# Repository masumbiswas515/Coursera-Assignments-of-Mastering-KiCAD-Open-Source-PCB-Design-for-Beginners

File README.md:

# Coursera-Assignments-of-Mastering-KiCAD-Open-Source-PCB-Design-for-Beginners
This respiratory consists of the peer graded assignments of the Coursera course, Mastering KiCAD: Open-Source PCB Design for Beginners.

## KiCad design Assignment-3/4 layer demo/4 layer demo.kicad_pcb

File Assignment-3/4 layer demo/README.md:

This folder contains all the KiCAD files.

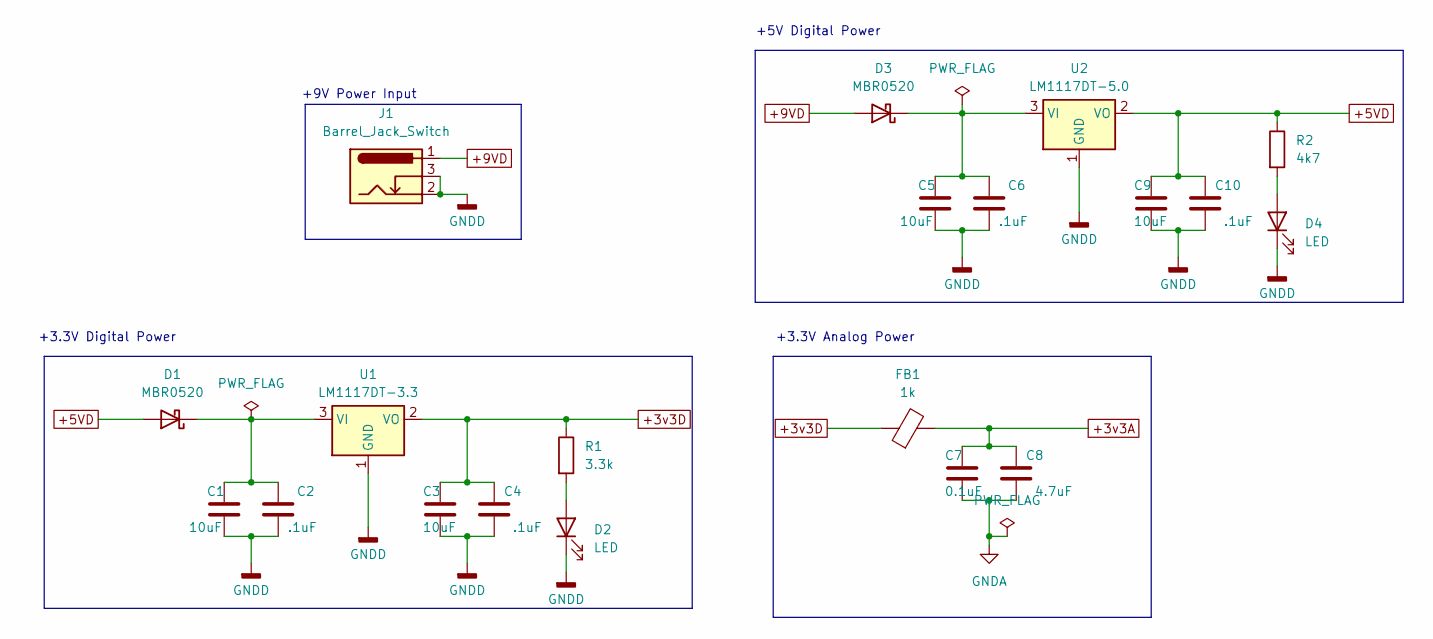
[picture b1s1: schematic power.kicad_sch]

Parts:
C1, C3, C5, C9: 10uF; C_0603_1608Metric
C2, C4, C6, C10: .1uF; C_0603_1608Metric
C7: 0.1uF; C_0603_1608Metric
C8: 4.7uF; C_0603_1608Metric
D1, D3: MBR0520; D_SOD-123
D2, D4: LED; LED_0603_1608Metric
FB1: 1k; L_0603_1608Metric
J1: Barrel_Jack_Switch; BarrelJack_Horizontal
R1: 3.3k; R_0603_1608Metric
R2: 4k7; R_0603_1608Metric
U1: LM1117DT-3.3; TO-252-3_TabPin2
U2: LM1117DT-5.0; TO-252-3_TabPin2

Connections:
+3v3A: C7.1, C8.1, FB1.2; also elsewhere on the board
+3v3D: C3.1, C4.1, FB1.1, R1.1, U1.2 (VO); also elsewhere on the board
+5VD: C9.1, C10.1, D1.2 (A), R2.1, U2.2 (VO)
+9VD: D3.2 (A), J1.1
GNDA: C7.2, C8.2; also elsewhere on the board
GNDD: C1.2, C2.2, C3.2, C4.2, C5.2, C6.2, C9.2, C10.2, D2.1 (K), D4.1 (K), J1.2, J1.3, U1.1 (GND), U2.1 (GND); also elsewhere on the board
unnamed: C1.1, C2.1, D1.1 (K), U1.3 (VI)
unnamed: D2.2 (A), R1.2
unnamed: C5.1, C6.1, D3.1 (K), U2.3 (VI)
unnamed: D4.2 (A), R2.2

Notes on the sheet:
+5V Digital Power
+9V Power Input
+3.3V Digital Power
+3.3V Analog Power

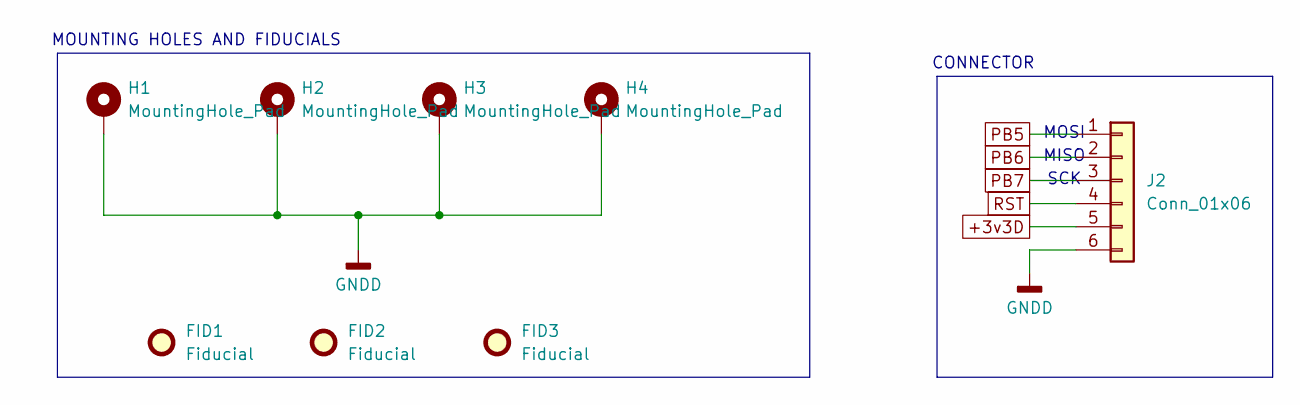
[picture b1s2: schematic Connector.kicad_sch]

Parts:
FID1, FID2, FID3: Fiducial; Fiducial_0.5mm_Mask1.5mm
H1, H2, H3, H4: MountingHole_Pad; MountingHole_2.2mm_M2_DIN965_Pad
J2: Conn_01x06; PinHeader_1x06_P1.00mm_Vertical

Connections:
+3v3D: J2.5; also elsewhere on the board
GNDD: H1.1, H2.1, H3.1, H4.1, J2.6; also elsewhere on the board
PB5: J2.1; also elsewhere on the board
PB6: J2.2; also elsewhere on the board
PB7: J2.3; also elsewhere on the board
RST: J2.4; also elsewhere on the board

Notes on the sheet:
MOSI
CONNECTOR
MOUNTING HOLES AND FIDUCIALS
SCK
MISO

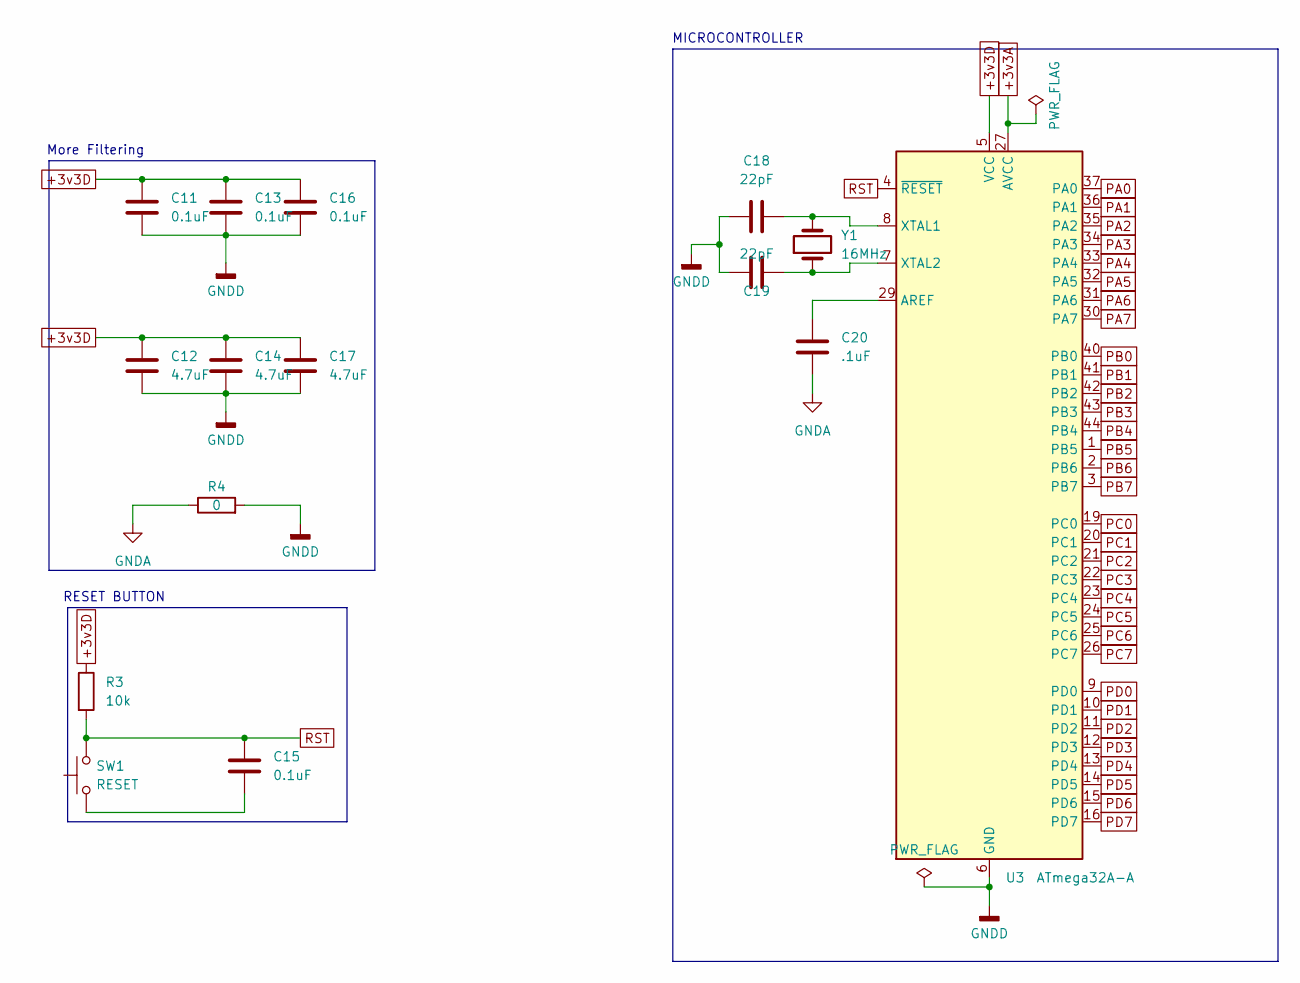
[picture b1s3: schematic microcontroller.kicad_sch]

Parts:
C11, C13, C15, C16: 0.1uF; C_0603_1608Metric
C12, C14, C17: 4.7uF; C_0603_1608Metric
C18, C19: 22pF; C_0603_1608Metric
C20: .1uF; C_0603_1608Metric
R3: 10k; R_0603_1608Metric
R4: 0; R_0603_1608Metric
SW1: RESET; SW_PUSH_6mm_H4.3mm
U3: ATmega32A-A; TQFP-44_10x10mm_P0.8mm
Y1: 16MHz; Crystal_SMD_0603-2Pin_6.0x3.5mm

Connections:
+3v3A: U3.27 (AVCC); also elsewhere on the board
+3v3D: C11.1, C12.1, C13.1, C14.1, C16.1, C17.1, R3.1, U3.5 (VCC), U3.17 (VCC), U3.38 (VCC); also elsewhere on the board
GNDA: C20.2, R4.1; also elsewhere on the board
GNDD: C11.2, C12.2, C13.2, C14.2, C16.2, C17.2, C18.1, C19.1, R4.2, U3.6 (GND), U3.18 (GND), U3.28 (GND), U3.39 (GND); also elsewhere on the board
unnamed: C15.2, SW1.1
unnamed: C20.1, U3.29 (AREF)
unnamed: C18.2, U3.8 (XTAL1), Y1.2
unnamed: C19.2, U3.7 (XTAL2), Y1.1
PA0: U3.37 (PA0)
PA1: U3.36 (PA1)
PA2: U3.35 (PA2)
PA3: U3.34 (PA3)
PA4: U3.33 (PA4)
PA5: U3.32 (PA5)
PA6: U3.31 (PA6)
PA7: U3.30 (PA7)
PB0: U3.40 (PB0)
PB1: U3.41 (PB1)
PB2: U3.42 (PB2)
PB3: U3.43 (PB3)
PB4: U3.44 (PB4)
PB5: U3.1 (PB5); also elsewhere on the board
PB6: U3.2 (PB6); also elsewhere on the board
PB7: U3.3 (PB7); also elsewhere on the board
PC0: U3.19 (PC0)
PC1: U3.20 (PC1)
PC2: U3.21 (PC2)
PC3: U3.22 (PC3)
PC4: U3.23 (PC4)
PC5: U3.24 (PC5)
PC6: U3.25 (PC6)
PC7: U3.26 (PC7)
PD0: U3.9 (PD0)
PD1: U3.10 (PD1)
PD2: U3.11 (PD2)
PD3: U3.12 (PD3)
PD4: U3.13 (PD4)
PD5: U3.14 (PD5)
PD6: U3.15 (PD6)
PD7: U3.16 (PD7)
RST: C15.1, R3.2, SW1.2, U3.4 (~RESET); also elsewhere on the board

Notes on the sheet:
MICROCONTROLLER
RESET BUTTON
More Filtering

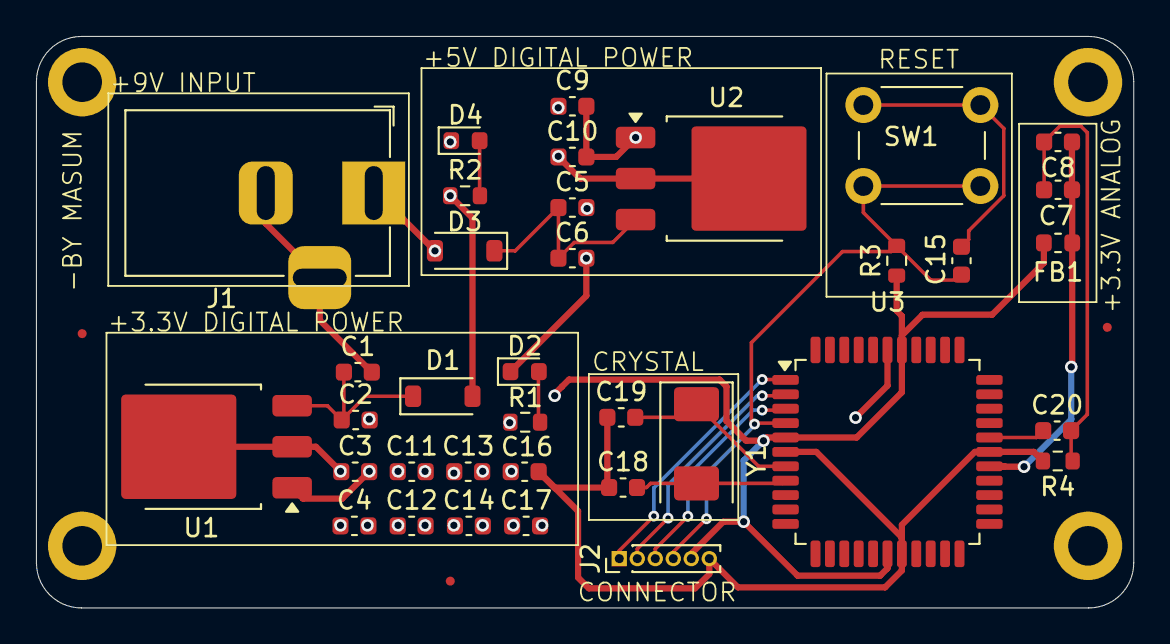
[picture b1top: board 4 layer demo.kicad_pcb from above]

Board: 4 copper layers, 61.0 x 31.8 mm, 43 parts (0 on the bottom side), 18 nets.

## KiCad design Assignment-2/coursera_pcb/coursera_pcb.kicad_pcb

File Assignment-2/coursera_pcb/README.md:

this folder contains the KiCAD files

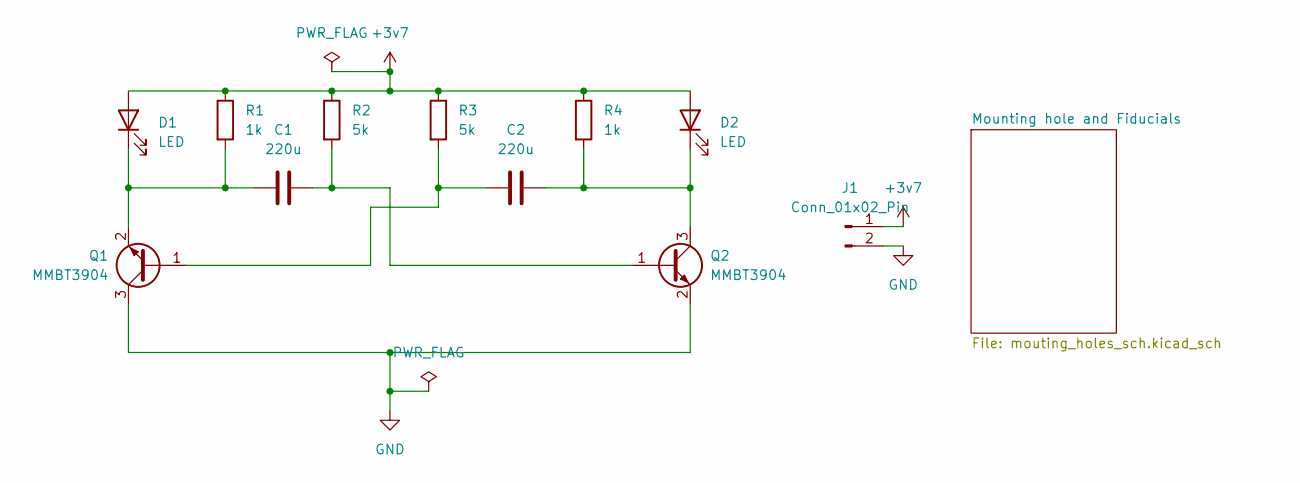
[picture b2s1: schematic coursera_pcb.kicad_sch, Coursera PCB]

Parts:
C1, C2: 220u; C_0805_2012Metric
D1, D2: LED; LED_0805_2012Metric
J1: Conn_01x02_Pin; PinHeader_1x02_P1.27mm_Vertical
Q1, Q2: MMBT3904; SOT-23
R1, R4: 1k; R_0805_2012Metric
R2, R3: 5k; R_0805_2012Metric

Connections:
+3v7: D1.2 (A), D2.2 (A), J1.1, R1.1, R2.1, R3.1, R4.1
GND: J1.2, Q1.3 (C), Q2.2 (E); also elsewhere on the board
unnamed: C1.1, D1.1 (K), Q1.2 (E), R1.2
unnamed: C2.2, D2.1 (K), Q2.3 (C), R4.2
unnamed: C2.1, Q1.1 (B), R3.2
unnamed: C1.2, Q2.1 (B), R2.2

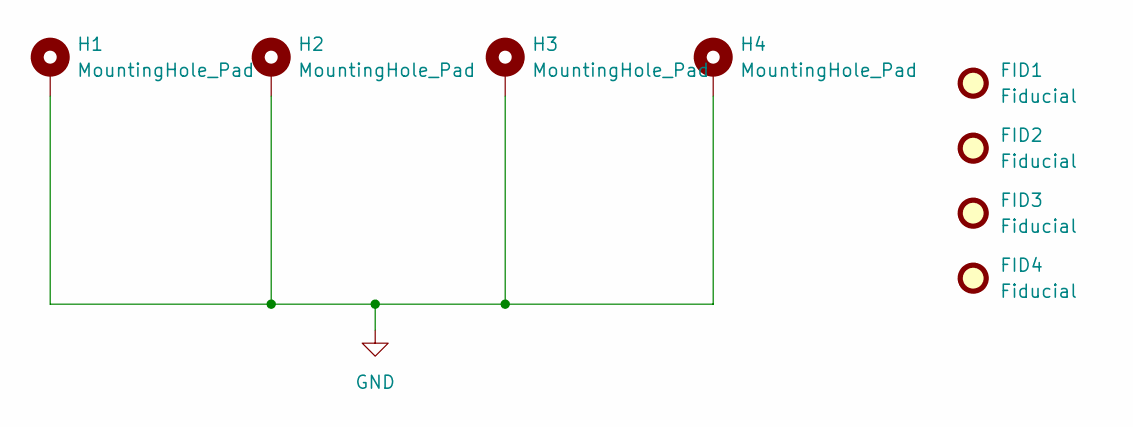
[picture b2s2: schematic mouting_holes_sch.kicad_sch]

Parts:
FID1, FID2, FID3, FID4: Fiducial; Fiducial_0.5mm_Mask1mm
H1, H2, H3, H4: MountingHole_Pad; MountingHole_2.5mm_Pad

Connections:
GND: H1.1, H2.1, H3.1, H4.1; also elsewhere on the board

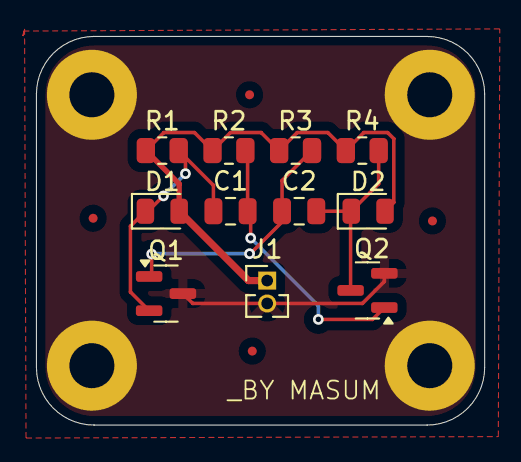
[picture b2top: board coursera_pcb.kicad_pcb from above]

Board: 2 copper layers, 24.9 x 21.6 mm, 19 parts (0 on the bottom side), 6 nets.

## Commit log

2025-05-29 Create Assignment-1
    This is the PDF of the assignment. I didn't save the KiCAD files for this assignment. I had rewritten this KiCAD for creating the 2nd Assignment.
2025-05-29 Update Assignment-1
2025-05-29 Add files via upload
    This is the PDF of the first assignment submission file.
2025-05-29 Add files via upload
    Both the pdf and gerber.
2025-05-29 Add files via upload
    the KiCAD files of assignment-2
